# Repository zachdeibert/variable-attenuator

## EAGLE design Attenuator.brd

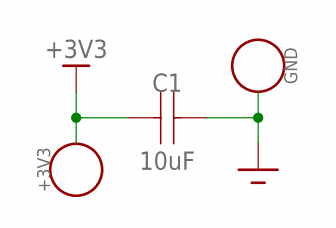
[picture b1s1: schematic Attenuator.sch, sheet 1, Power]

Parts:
C1: 10uF; 0805
TP1: +3V3; ALIGATOR-PAD
TP2: GND; ALIGATOR-PAD

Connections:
+3V3: C1.P$1, TP1.P$1, TP1.P$2, TP1.P$3, TP1.P$4, TP1.P$5, TP1.P$6; also elsewhere on the board
GND: C1.P$2, TP2.P$1, TP2.P$2, TP2.P$3, TP2.P$4, TP2.P$5, TP2.P$6; also elsewhere on the board

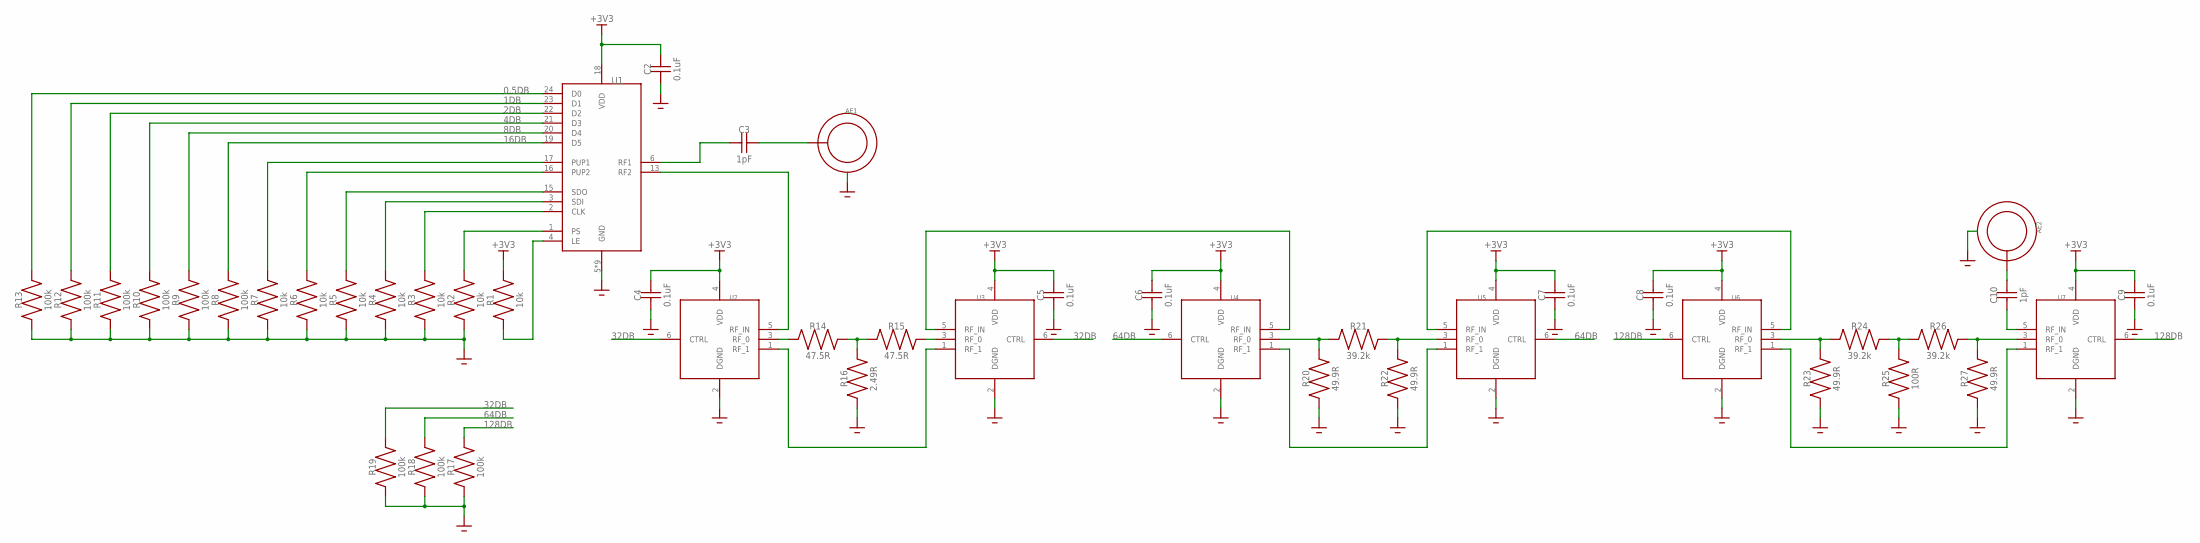
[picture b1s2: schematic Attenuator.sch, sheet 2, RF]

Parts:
AE1, AE2: CON-SMA-EDGE-S
C2, C4, C5, C6, C7, C8, C9: 0.1uF; 0805
C3, C10: 1pF; 0805
R1, R2, R3, R4, R5, R6, R7: 10k; 0805
R8, R9, R10, R11, R12, R13, R17, R18, R19: 100k; 0805
R14, R15: 47.5R; 0805
R16: 2.49R; 0805
R20, R22, R23, R27: 49.9R; 0805
R21, R24, R26: 39.2k; 0805
R25: 100R; 0805
U1: SKY12347-362LF; QFN50P400X400X100-25T270N
U2, U3, U4, U5, U6, U7: BGS12SN6E6327XTSA1; SON40P70X110X40-6N

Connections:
0.5DB: R13.P$2, U1.24 (D0); also elsewhere on the board
1DB: R12.P$2, U1.23 (D1); also elsewhere on the board
2DB: R11.P$2, U1.22 (D2); also elsewhere on the board
4DB: R10.P$2, U1.21 (D3); also elsewhere on the board
8DB: R9.P$2, U1.20 (D4); also elsewhere on the board
16DB: R8.P$2, U1.19 (D5); also elsewhere on the board
32DB: R19.P$2, U2.6 (CTRL), U3.6 (CTRL); also elsewhere on the board
64DB: R18.P$2, U4.6 (CTRL), U5.6 (CTRL); also elsewhere on the board
128DB: R17.P$2, U6.6 (CTRL), U7.6 (CTRL); also elsewhere on the board
+3V3: C2.P$2, C4.P$2, C5.P$2, C6.P$2, C7.P$2, C8.P$2, C9.P$2, R1.P$2, U1.18 (VDD), U2.4 (VDD), U3.4 (VDD), U4.4 (VDD), U5.4 (VDD), U6.4 (VDD), U7.4 (VDD); also elsewhere on the board
GND: AE1.GND1 (GND), AE1.GND2 (GND), AE1.GND3 (GND), AE1.GND4 (GND), AE2.GND1 (GND), AE2.GND2 (GND), AE2.GND3 (GND), AE2.GND4 (GND), C2.P$1, C4.P$1, C5.P$1, C6.P$1, C7.P$1, C8.P$1, C9.P$1, R2.P$1, R3.P$1, R4.P$1, R5.P$1, R6.P$1, R7.P$1, R8.P$1, R9.P$1, R10.P$1, R11.P$1, R12.P$1, R13.P$1, R16.P$1, R17.P$1, R18.P$1, R19.P$1, R20.P$1, R22.P$1, R23.P$1, R25.P$1, R27.P$1, U1.5 (GND), U1.7 (GND), U1.8 (GND), U1.9 (GND), U1.10 (GND), U1.11 (GND), U1.12 (GND), U1.14 (GND), U1.25 (GND), U2.2 (DGND), U3.2 (DGND), U4.2 (DGND), U5.2 (DGND), U6.2 (DGND), U7.2 (DGND); also elsewhere on the board
unnamed: C3.P$1, U1.6 (RF1)
unnamed: AE1.CENTER (OUT), C3.P$2
unnamed: R1.P$1, U1.4 (LE)
unnamed: R2.P$2, U1.1 (PS)
unnamed: R3.P$2, U1.2 (CLK)
unnamed: R4.P$2, U1.3 (SDI)
unnamed: R5.P$2, U1.15 (SDO)
unnamed: R6.P$2, U1.16 (PUP2)
unnamed: R7.P$2, U1.17 (PUP1)
unnamed: U1.13 (RF2), U2.5 (RF_IN)
unnamed: R14.P$1, U2.3 (RF_0)
unnamed: R14.P$2, R15.P$1, R16.P$2
unnamed: R15.P$2, U3.3 (RF_0)
unnamed: U2.1 (RF_1), U3.1 (RF_1)
unnamed: U3.5 (RF_IN), U4.5 (RF_IN)
unnamed: R20.P$2, R21.P$1, U4.3 (RF_0)
unnamed: R21.P$2, R22.P$2, U5.3 (RF_0)
unnamed: U4.1 (RF_1), U5.1 (RF_1)
unnamed: U5.5 (RF_IN), U6.5 (RF_IN)
unnamed: R23.P$2, R24.P$1, U6.3 (RF_0)
unnamed: R24.P$2, R25.P$2, R26.P$1
unnamed: R26.P$2, R27.P$2, U7.3 (RF_0)
unnamed: U6.1 (RF_1), U7.1 (RF_1)
unnamed: C10.P$1, U7.5 (RF_IN)
unnamed: AE2.CENTER (OUT), C10.P$2

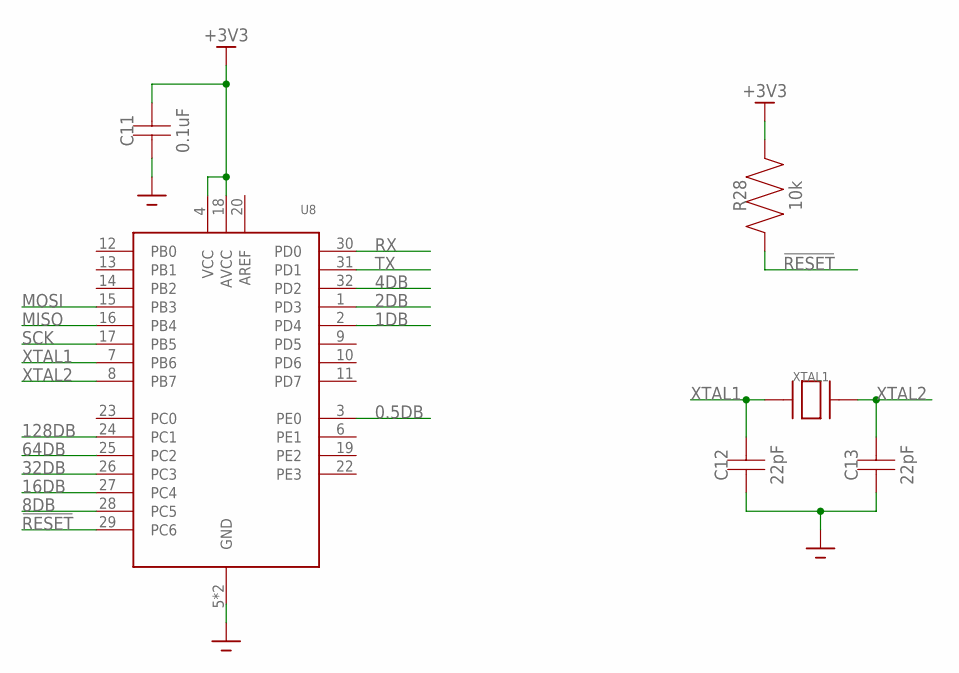
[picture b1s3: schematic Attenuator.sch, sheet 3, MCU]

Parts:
C11: 0.1uF; 0805
C12, C13: 22pF; 0805
R28: 10k; 0805
U8: ATMEGA328PB32-TQFP; QFP80P900X900X120-32
XTAL1: CRYSTAL; ABM2

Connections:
0.5DB: U8.3 (PE0); also elsewhere on the board
1DB: U8.2 (PD4); also elsewhere on the board
2DB: U8.1 (PD3); also elsewhere on the board
4DB: U8.32 (PD2); also elsewhere on the board
8DB: U8.28 (PC5); also elsewhere on the board
16DB: U8.27 (PC4); also elsewhere on the board
32DB: U8.26 (PC3); also elsewhere on the board
64DB: U8.25 (PC2); also elsewhere on the board
128DB: U8.24 (PC1); also elsewhere on the board
!RESET: R28.P$1, U8.29 (PC6); also elsewhere on the board
+3V3: C11.P$2, R28.P$2, U8.4 (VCC), U8.18 (AVCC); also elsewhere on the board
AREF: U8.20 (AREF)
GND: C11.P$1, C12.P$1, C13.P$1, U8.5 (GND), U8.21 (GND); also elsewhere on the board
MISO: U8.16 (PB4); also elsewhere on the board
MOSI: U8.15 (PB3); also elsewhere on the board
RX: U8.30 (PD0); also elsewhere on the board
SCK: U8.17 (PB5); also elsewhere on the board
TX: U8.31 (PD1); also elsewhere on the board
XTAL1: C12.P$2, U8.7 (PB6), XTAL1.P$1
XTAL2: C13.P$2, U8.8 (PB7), XTAL1.P$2

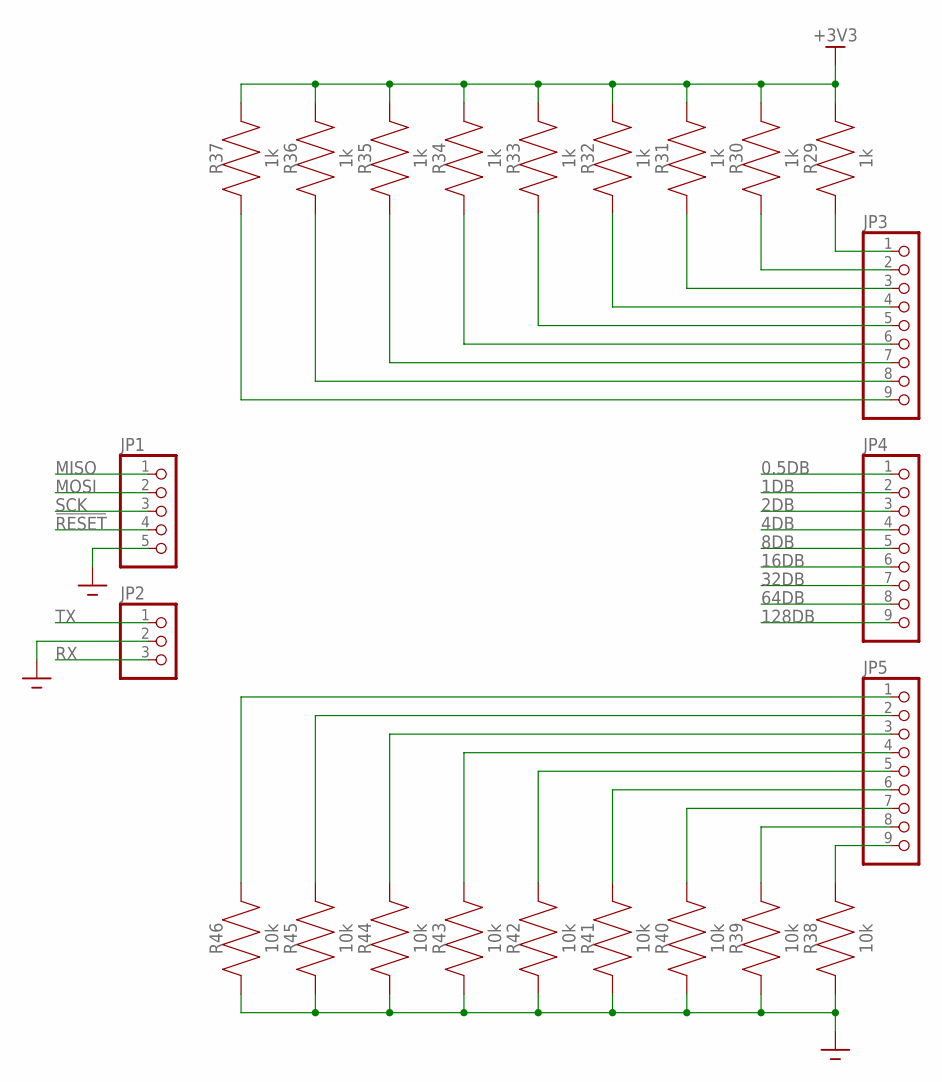
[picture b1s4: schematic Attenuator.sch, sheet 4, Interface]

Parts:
JP1: PINHD-1X5; 1X05
JP2: PINHD-1X3; 1X03
JP3, JP4, JP5: PINHD-1X9; 1X09
R29, R30, R31, R32, R33, R34, R35, R36, R37: 1k; 0805
R38, R39, R40, R41, R42, R43, R44, R45, R46: 10k; 0805

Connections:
0.5DB: JP4.1; also elsewhere on the board
1DB: JP4.2; also elsewhere on the board
2DB: JP4.3; also elsewhere on the board
4DB: JP4.4; also elsewhere on the board
8DB: JP4.5; also elsewhere on the board
16DB: JP4.6; also elsewhere on the board
32DB: JP4.7; also elsewhere on the board
64DB: JP4.8; also elsewhere on the board
128DB: JP4.9; also elsewhere on the board
!RESET: JP1.4; also elsewhere on the board
+3V3: R29.P$2, R30.P$2, R31.P$2, R32.P$2, R33.P$2, R34.P$2, R35.P$2, R36.P$2, R37.P$2; also elsewhere on the board
GND: JP1.5, JP2.2, R38.P$1, R39.P$1, R40.P$1, R41.P$1, R42.P$1, R43.P$1, R44.P$1, R45.P$1, R46.P$1; also elsewhere on the board
MISO: JP1.1; also elsewhere on the board
MOSI: JP1.2; also elsewhere on the board
unnamed: JP3.1, R29.P$1
unnamed: JP3.2, R30.P$1
unnamed: JP3.3, R31.P$1
unnamed: JP3.4, R32.P$1
unnamed: JP3.5, R33.P$1
unnamed: JP3.6, R34.P$1
unnamed: JP3.7, R35.P$1
unnamed: JP3.8, R36.P$1
unnamed: JP3.9, R37.P$1
unnamed: JP5.9, R38.P$2
unnamed: JP5.8, R39.P$2
unnamed: JP5.7, R40.P$2
unnamed: JP5.6, R41.P$2
unnamed: JP5.5, R42.P$2
unnamed: JP5.4, R43.P$2
unnamed: JP5.3, R44.P$2
unnamed: JP5.2, R45.P$2
unnamed: JP5.1, R46.P$2
RX: JP2.3; also elsewhere on the board
SCK: JP1.3; also elsewhere on the board
TX: JP2.1; also elsewhere on the board

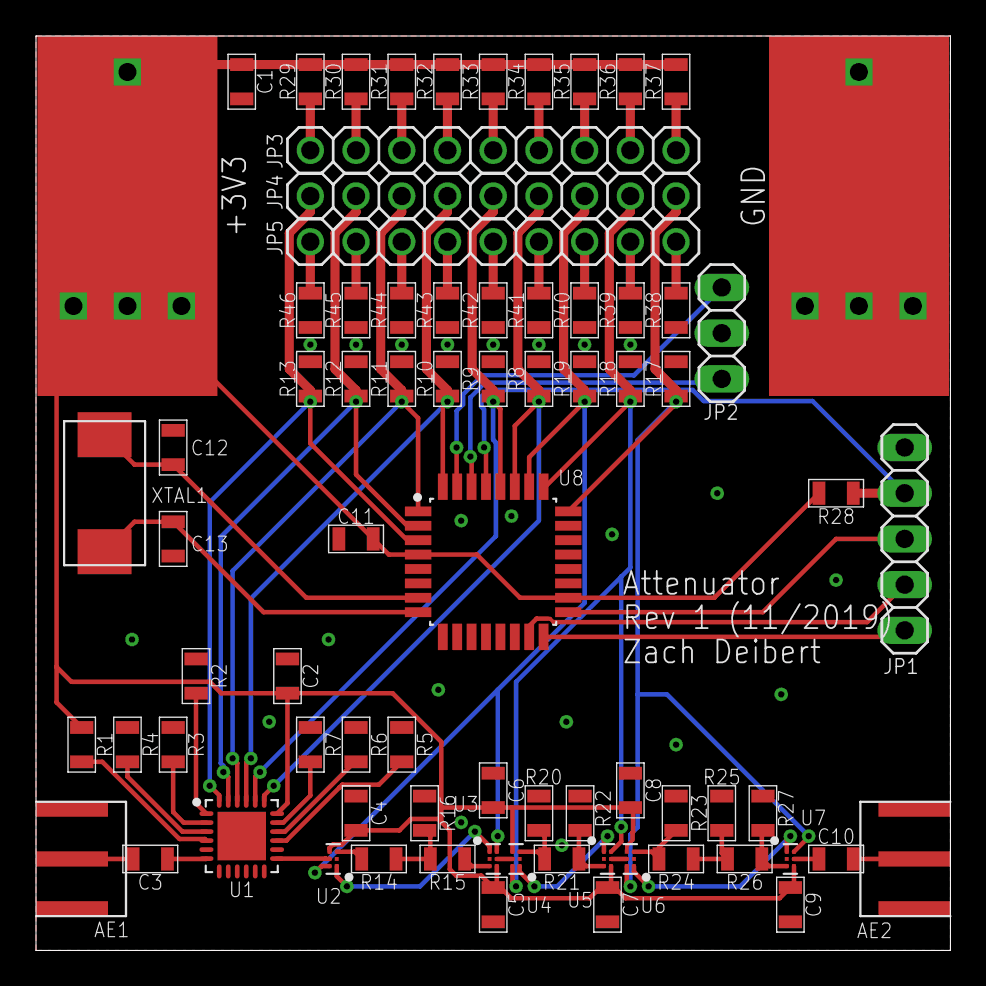
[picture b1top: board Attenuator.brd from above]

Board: 2 copper layers, 50.8 x 50.8 mm, 77 parts (0 on the bottom side), 62 nets.
